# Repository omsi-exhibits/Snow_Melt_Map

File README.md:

# Snow Melt Map Notes
The electronics consist of a custom button controller pcb titled 8x_button_io_board that sends button press
commands to a octoWS2811 adapter with a teensy 4.0 socketed in it. The data sent over serial hand twisted
cable that is around 7 feet long. At a baud rate of 9600. 

addressable rgb led channels with a mcu to control the leds. The current mcu is Adafruit ItsyBitsy M0 express
with a plan to switch to a Teensy 4.0 if more pins or processing power is needed.

## Folder organization
- pcb :: contains eagle pcb files: 8x_button_io_board
- src :: main source code for the led controller 
- docs :: documentation, system diagram, map_led_hole numbering, river_segment_indexes, data sheets
- button_controller_arduino :: code for the button controller
- audio :: audio assets to be used with the wavTrigger board
- examples_tests :: quick tests used to guide prototype direction

## Led Lights
WS2813B  WS2812 code compatible. These leds have 2 data channels incase one led breaks the
backup data channel will be used. This allows the strip to skip a bad led and continue.

## Power Calculations
550 leds 48ma each LED when light at max. The led strings come in 50 led segments. We need power injection every 50 leds at least.
So that is 11 + 1 the end of the strip. 50 Leds at 48mA is 2.4A.

### Total Max Power usage
550 leds * 48mA = 26400mA, If all the leds are on at full brightness.
Power supply is a LRS-200-5 5v 200W output
(Wire Ampacity) [https://en.wikipedia.org/wiki/American_wire_gauge#Tables_of_AWG_wire_sizes]

### Fused Power distro board
(falcon f-8 power distro board) [https://www.pixelcontroller.com/store/accessories/46-f8-distro.html]
There are two power distribution boards with 8 5A fuse holders. The fuse holders take mini blade ATX fuses.

Useful fuse links
(all about fuses for led projects) [https://www.doityourselfchristmas.com/wiki/index.php?title=Power_Supplies#Using_Fuses_and_Fuseholders]
(assorted fuses) [https://www.amazon.com/Bussmann-NO-43-Blade-Tester-Puller/dp/B000DCN9BW]
(fuse holder board mount) [https://www.keyelco.com/product.cfm/Mini-Auto-Fuse-Holders/3544-2/product_id/1376]
(fuse holder mini ATM) [https://www.digikey.com/en/products/detail/keystone-electronics/3568/2137306]

# SNOW MELT MAP Button Target Areas
// Button 1 - Colorado R. & Tributaries
// --- R14 - R34
// Button 2 - Snow Monitoring Sites
// Button 3 - Dams (7)
// Button 4 - Los Vegas City, Dams, and river segments feeding Los Vegas. 
// --- R14 - R30 light up & 4 Dams (Lighting up Damns seems wrong, but maybe okay)
// Button 5 - Farms
// Button 6 - Grand Junction City, Dam, and rivers to the right of the city leading into it
// --- R21b (sub segment) (0-12leds) & R22, Dam
// Button 7 - Greater Los Angeles water supply
// --- Aqueducts too
// --- All river supply. exclude R34
// Button 8 -  (Long-distance water users) Outside Colorado r. Watershed
// --- All Water supply areas.

Once a button is pressed  - Only 1 button may be active at a time.
UI - dim all the currently lit segments and lights then activate what was pressed
Good opportunity for a fade in and fade out sound.

If the on button is pressed it turns the feature off.
If left on after a set time it can return to attractor mode. 

## Programing Notes
LedSegment defines a segment of leds, and their connection point to others.
LedRegion collects LedSegments and has state. The LedRegion can be interacted with.
- TurnedOn, TurnedOff, RiverOn, RiverOff.
- LedModule(Segment) that are for the Dams, etc. Should not store color data in their object.

## FastLED notes:
Colors are always dimmed down by a fraction. The dimming fraction is expressed in 256ths, so if you wanted to dim a color down by 25% of its current brightness, you first have to express that in 256ths. In this case, 25% = 64/256.
```cpp
  // Dim a color by 25% (64/256ths)
  // using "video" scaling, meaning: never fading to full black
  leds[i].fadeLightBy( 64 );
```
The library also provides a function that lets you 'clamp' each of the RGB channels to be within given minimums and maximums. 

Blending colors amountOfP2 is 0 - 255. 128 is 50% 255 is 100 color p2.
```cpp 
CRGB 	blend (const CRGB &p1, const CRGB &p2, fract8 amountOfP2)
```

## Hardware Purchased:
[WS2813 LEDs from raywu](https://www.aliexpress.com/item/32733155461.html)
[Aliexpress Neopixel store - Ray Wu](https://www.aliexpress.com/store/701799?spm=a2g0o.detail.1000002.2.75cff4f3j9F8uI)
LRS-200-5

## LED quality testing
I have determined that the last batch of hardware had some defects that likely were contributing to the intermittent problems
with leds flickering and possible temperature based issues.
We ordered more led strands to try to solve the issue. This time we got about 2x the leds we will need incase we run into the
same issues and need to pick the best leds from the pack.

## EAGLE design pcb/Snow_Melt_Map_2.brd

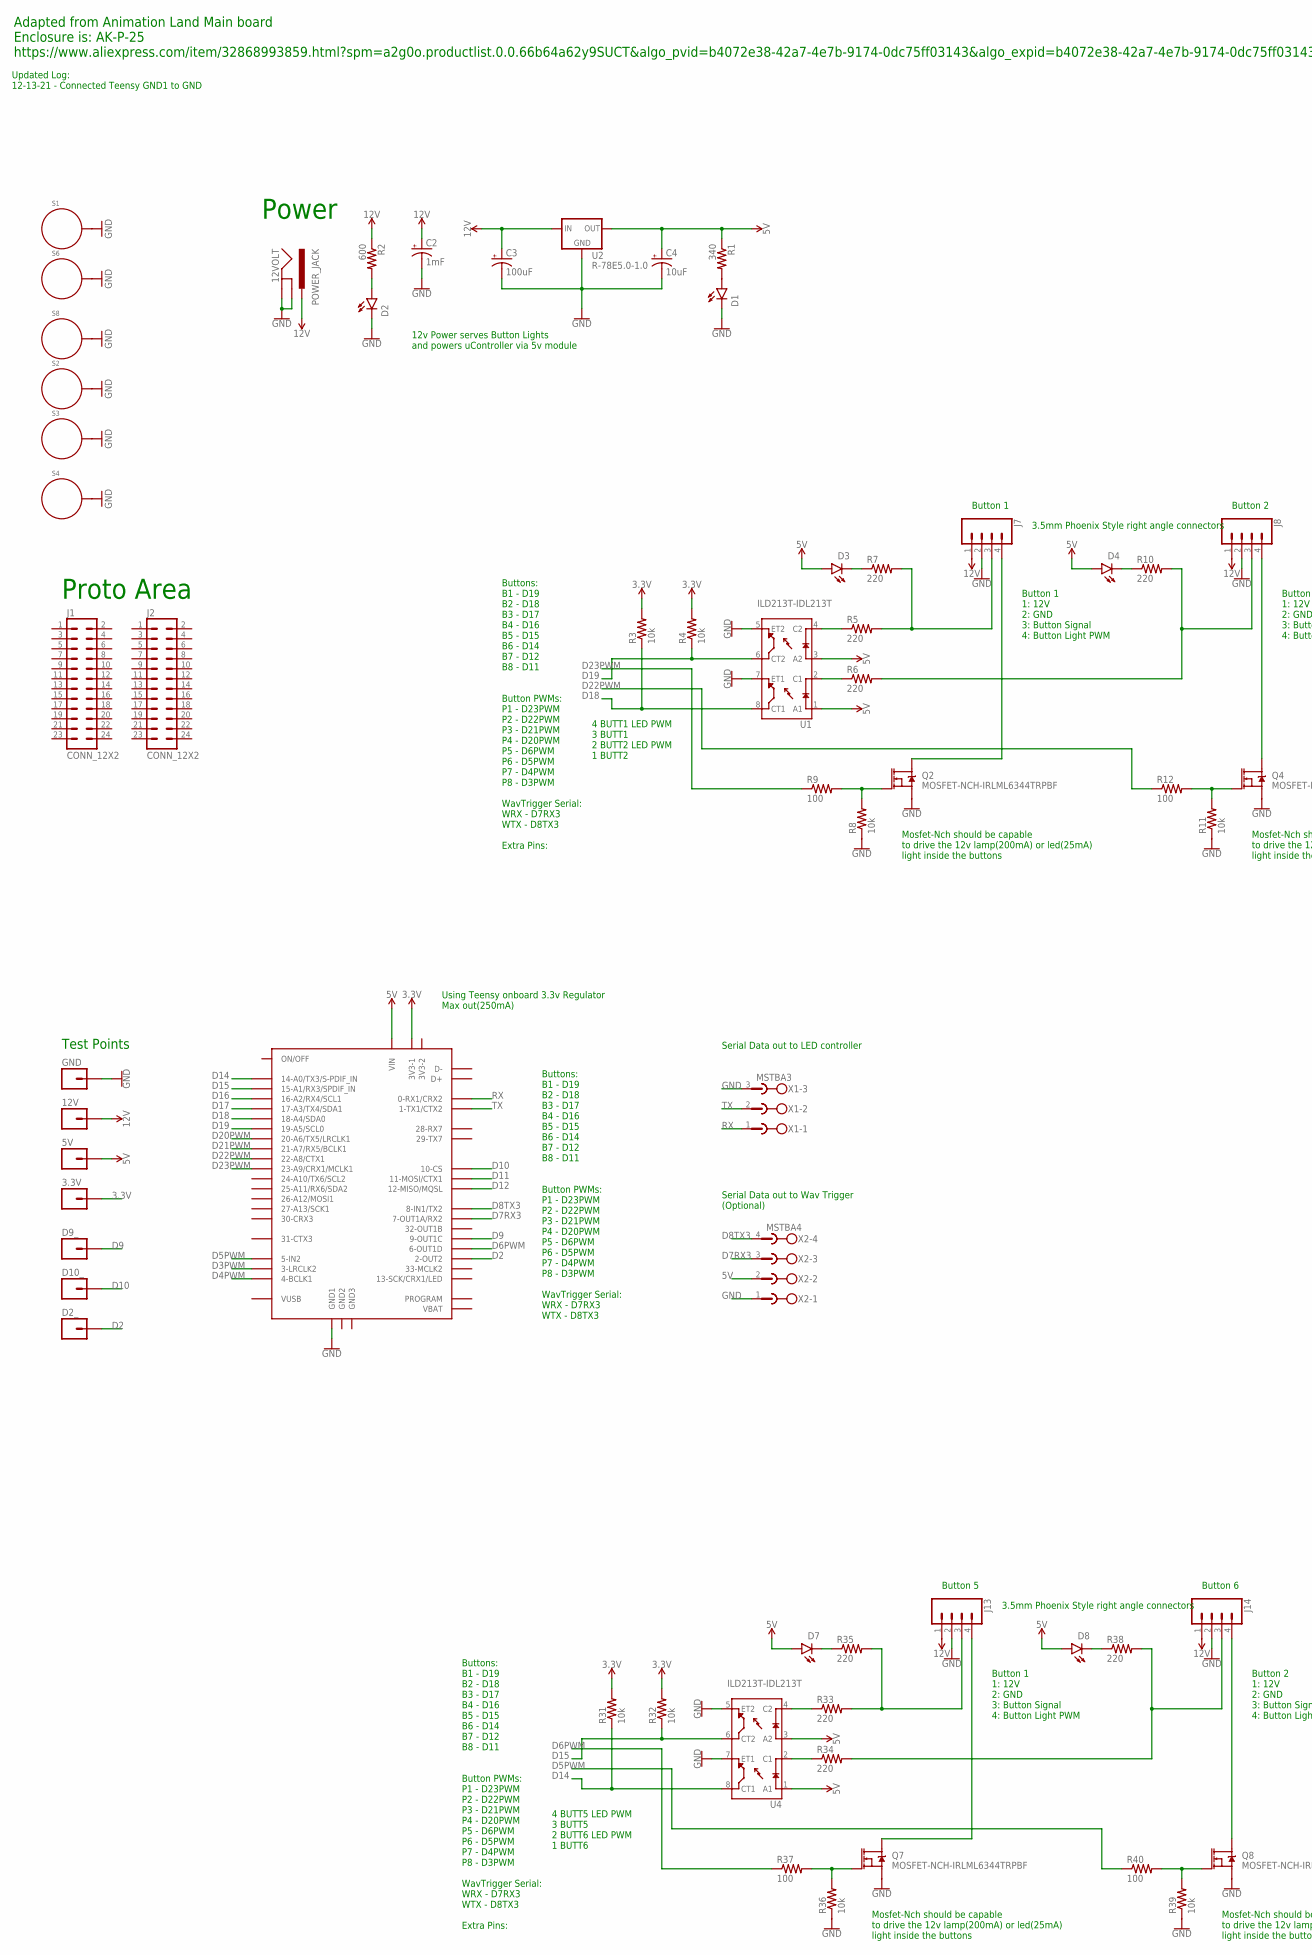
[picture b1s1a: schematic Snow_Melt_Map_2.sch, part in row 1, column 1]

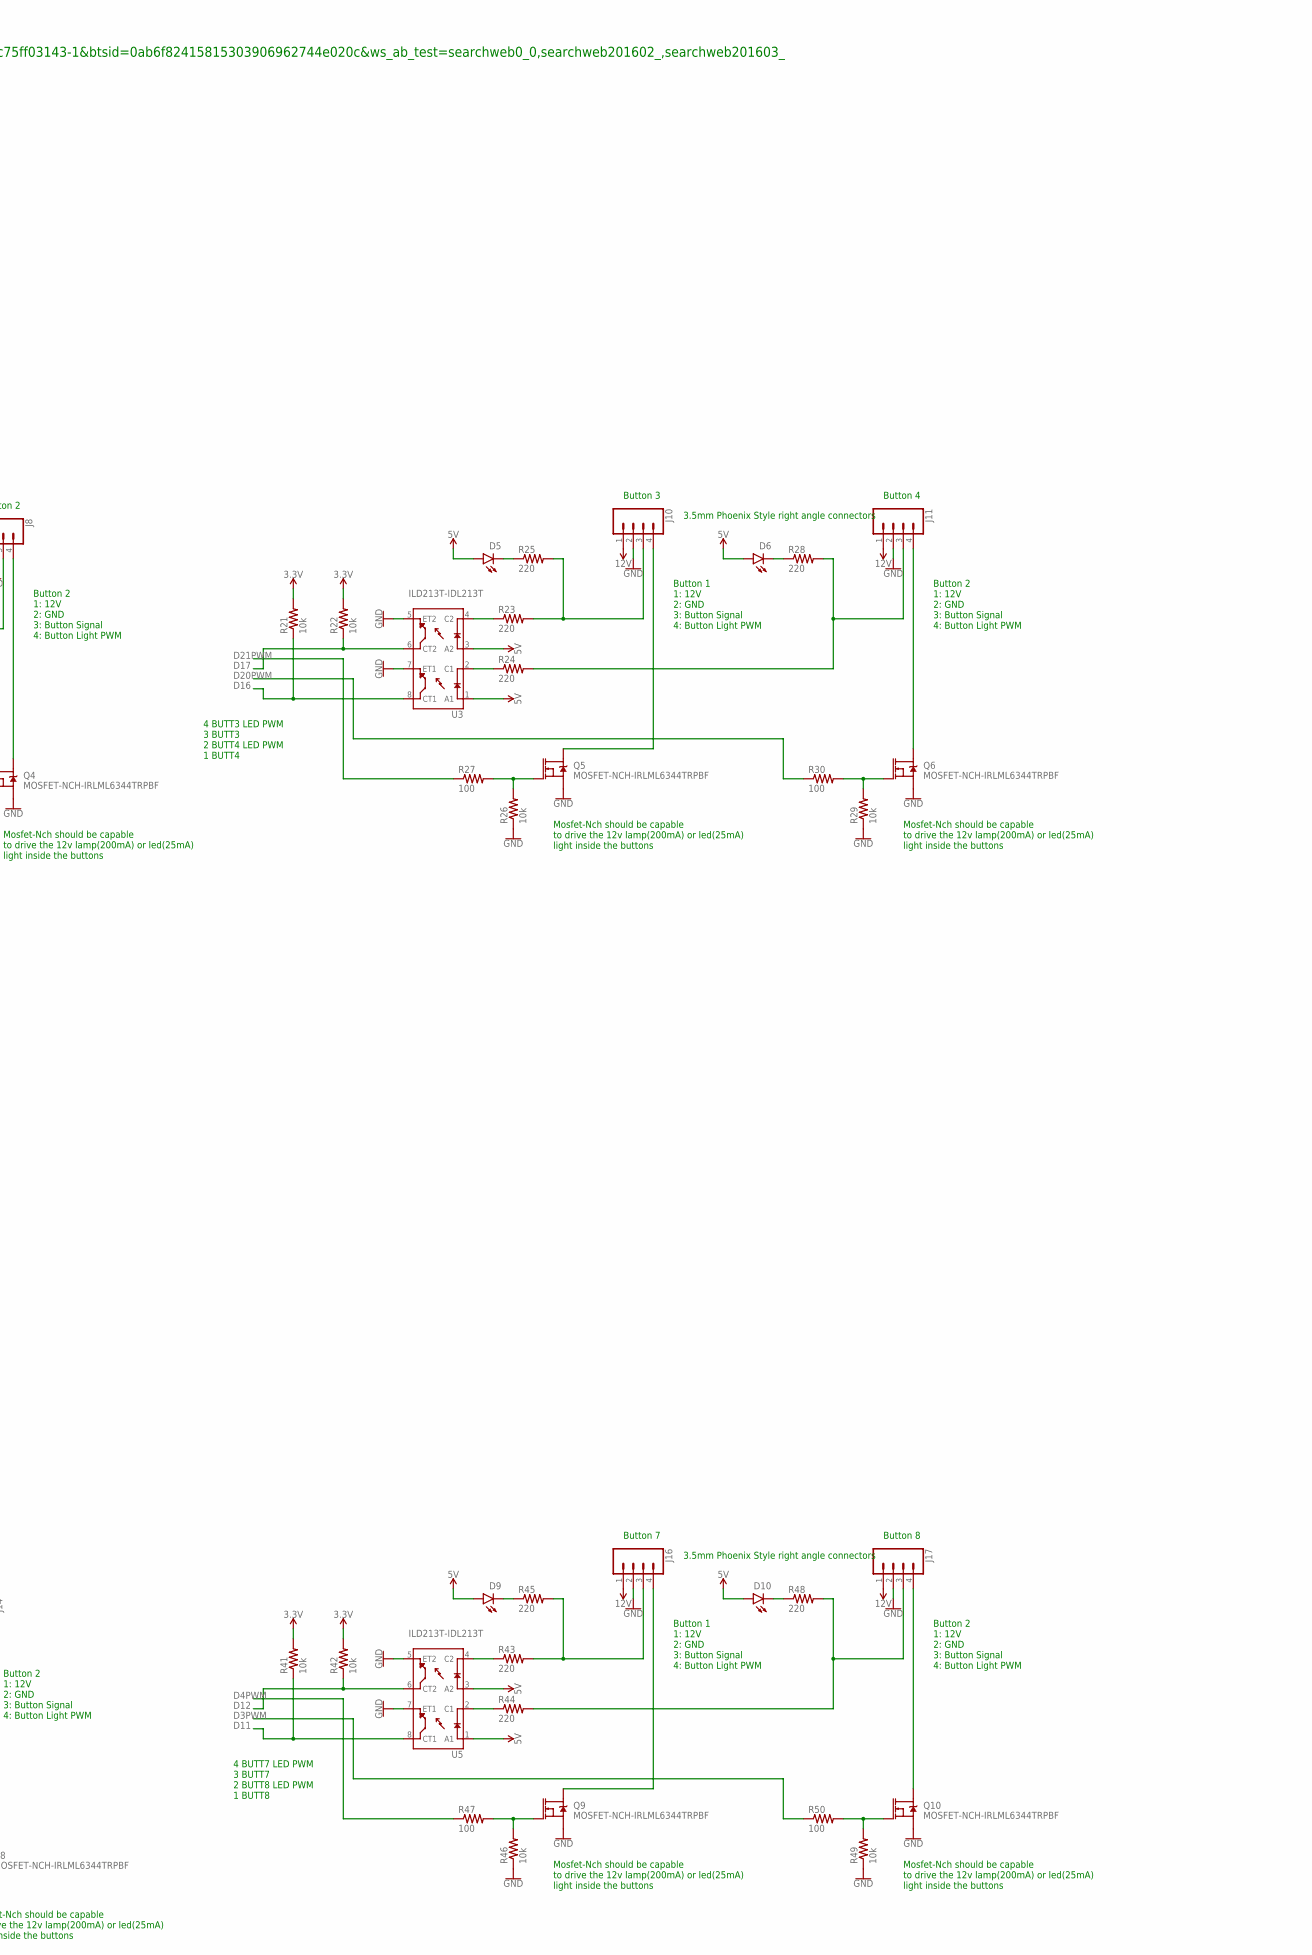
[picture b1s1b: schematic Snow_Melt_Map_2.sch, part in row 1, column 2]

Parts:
3.3V, 5V, 12V: M01PTH; 1X01
12VOLT: POWER_JACK; POWER_JACK_PTH
C2: 1mF; CPOL-RADIAL-5MM-10MM
C3: 100uF; CPOL-RADIAL-2.5MM-6.5MM
C4: 10uF; CPOL-RADIAL-2.5MM-5MM-KIT
D1, D2, D3, D4, D5, D6, D7, D8, D9, D10: RED; LED-1206
D2_, D9_, D10_: M01PTH; 1X01
GND: M01PTH; 1X01
J1, J2: CONN_12X2; 2X12
J7, J8, J10, J11, J13, J14, J16, J17: CONN_043.5MM_RA; 1X04_3.5MM_RA
Q2, Q4, Q5, Q6, Q7, Q8, Q9, Q10: MOSFET-NCH-IRLML6344TRPBF; SOT23-3
R1: 340; R0805
R2: 600; R0805
R3, R4, R8, R11, R21, R22, R26, R29, R31, R32, R36, R39, R41, R42, R46, R49: 10k; R0805
R5, R6, R7, R10, R23, R24, R25, R28, R33, R34, R35, R38, R43, R44, R45, R48: 220; R0805
R9, R12, R27, R30, R37, R40, R47, R50: 100; R0805
S1, S2, S3, S4, S6, S8: STANDOFF_ELECTRICAL5-32; STANDOFF_ELECTRICAL_5_32
U1, U3, U4, U5: ILD213T-IDL213T; SO08
U2: R-78E5.0-1.0; DC-DC_CONVERTER_78XX
U$1: TEENSY40
X1: MSTBA3
X2: MSTBA4

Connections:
3.3V: 3.3V.1, R3.2, R4.2, R21.2, R22.2, R31.2, R32.2, R41.2, R42.2, U$1.3V3-1
5V: 5V.1, C4.1 (+), D3.A, D4.A, D5.A, D6.A, D7.A, D8.A, D9.A, D10.A, R1.1, U1.1 (A1), U1.3 (A2), U2.VOUT (OUT), U3.1 (A1), U3.3 (A2), U4.1 (A1), U4.3 (A2), U5.1 (A1), U5.3 (A2), U$1.VIN, X2.2
12V: 12V.1, 12VOLT.PWR, C2.+, C3.1 (+), J7.1, J8.1, J10.1, J11.1, J13.1, J14.1, J16.1, J17.1, R2.1, U2.VIN (IN)
D2: D2_.1, U$1.2-OUT2
D3PWM: R50.1, U$1.3-LRCLK2
D4PWM: R47.1, U$1.4-BCLK2 (4-BCLK1)
D5PWM: R40.1, U$1.5-IN2
D6PWM: R37.1, U$1.6-OUT1D
D7RX3: U$1.7-RX2/OUT1A (7-OUT1A/RX2), X2.3
D8TX3: U$1.8-TX2/IN1 (8-IN1/TX2), X2.4
D9: D9_.1, U$1.9-OUT1C
D10: D10_.1, U$1.10-CS/MQSR (10-CS)
D11: R41.1, U5.8 (CT1), U$1.11-MOSI/CTX1
D12: R42.1, U5.6 (CT2), U$1.12-MIO/MQSL (12-MISO/MQSL)
D14: R31.1, U4.8 (CT1), U$1.14-A0/TX3/S-PFI_OUT (14-A0/TX3/S-PDIF_IN)
D15: R32.1, U4.6 (CT2), U$1.15-A1/RX3/S-PDIF_IN (15-A1/RX3/SPDIF_IN)
D16: R21.1, U3.8 (CT1), U$1.16-A2/RX4/SCL1
D17: R22.1, U3.6 (CT2), U$1.17-A3/TX4/SDA1
D18: R3.1, U1.8 (CT1), U$1.18-A4/SDA0
D19: R4.1, U1.6 (CT2), U$1.19-A5/SCL0
D20PWM: R30.1, U$1.20-A6/TX5/LRCLK1
D21PWM: R27.1, U$1.21-A7/RX5/BCLK1
D22PWM: R12.1, U$1.22-A8/CTX1
D23PWM: R9.1, U$1.23-A9/CRX1/CCLK1 (23-A9/CRX1/MCLK1)
GND: 12VOLT.GND, 12VOLT.GNDBREAK, C2.-, C3.2 (-), C4.2 (-), D1.C, D2.C, GND.1, J7.2, J8.2, J10.2, J11.2, J13.2, J14.2, J16.2, J17.2, Q2.2 (S), Q4.2 (S), Q5.2 (S), Q6.2 (S), Q7.2 (S), Q8.2 (S), Q9.2 (S), Q10.2 (S), R8.1, R11.1, R26.1, R29.1, R36.1, R39.1, R46.1, R49.1, S1.P1, S2.P1, S3.P1, S4.P1, S6.P1, S8.P1, U1.5 (ET2), U1.7 (ET1), U2.GND, U3.5 (ET2), U3.7 (ET1), U4.5 (ET2), U4.7 (ET1), U5.5 (ET2), U5.7 (ET1), U$1.GND1, X1.3, X2.1
unnamed: D1.A, R1.2
unnamed: D2.A, R2.2
unnamed: J7.3, R5.2, R7.2
unnamed: D3.C, R7.1
unnamed: R5.1, U1.4 (C2)
unnamed: R6.1, U1.2 (C1)
unnamed: Q2.1 (G), R8.2, R9.2
unnamed: J7.4, Q2.3 (D)
unnamed: J8.3, R6.2, R10.2
unnamed: D4.C, R10.1
unnamed: Q4.1 (G), R11.2, R12.2
unnamed: J8.4, Q4.3 (D)
unnamed: J10.3, R23.2, R25.2
unnamed: D5.C, R25.1
unnamed: R23.1, U3.4 (C2)
unnamed: R24.1, U3.2 (C1)
unnamed: Q5.1 (G), R26.2, R27.2
unnamed: J10.4, Q5.3 (D)
unnamed: J11.3, R24.2, R28.2
unnamed: D6.C, R28.1
unnamed: Q6.1 (G), R29.2, R30.2
unnamed: J11.4, Q6.3 (D)
unnamed: J13.3, R33.2, R35.2
unnamed: D7.C, R35.1
unnamed: R33.1, U4.4 (C2)
unnamed: R34.1, U4.2 (C1)
unnamed: Q7.1 (G), R36.2, R37.2
unnamed: J13.4, Q7.3 (D)
unnamed: J14.3, R34.2, R38.2
unnamed: D8.C, R38.1
unnamed: Q8.1 (G), R39.2, R40.2
unnamed: J14.4, Q8.3 (D)
unnamed: J16.3, R43.2, R45.2
unnamed: D9.C, R45.1
unnamed: R43.1, U5.4 (C2)
unnamed: R44.1, U5.2 (C1)
unnamed: Q9.1 (G), R46.2, R47.2
unnamed: J16.4, Q9.3 (D)
unnamed: J17.3, R44.2, R48.2
unnamed: D10.C, R48.1
unnamed: Q10.1 (G), R49.2, R50.2
unnamed: J17.4, Q10.3 (D)
RX: U$1.0-RX1 (0-RX1/CRX2), X1.1
TX: U$1.1-TX1 (1-TX1/CTX2), X1.2

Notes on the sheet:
Adapted from Animation Land Main board Enclosure is: AK-P-25 https://www.aliexpress.com/item/32868993859.html?spm=a2g0o.productlist.0.0.66b64a62y9SUCT&algo_pvid=b4072e38-42a7-4e7b-9174-0dc75ff03143&algo_expid=b4072e38-42a7-4e7b-9174-0dc75ff03143-1&btsid=0ab6f82415815303906962744e020c&ws_ab_test=sea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
Proto Area
Mosfet-Nch should be capable to drive the 12v lamp(200mA) or led(25mA) light inside the buttons
4 BUTT1 LED PWM 3 BUTT1 2 BUTT2 LED PWM 1 BUTT2
Button 1 1: 12V 2: GND 3: Button Signal 4: Button Light PWM
Button 2 1: 12V 2: GND 3: Button Signal 4: Button Light PWM
3.5mm Phoenix Style right angle connectors
Button 1
Button 2
4 BUTT3 LED PWM 3 BUTT3 2 BUTT4 LED PWM 1 BUTT4
Button 3
Button 4
4 BUTT5 LED PWM 3 BUTT5 2 BUTT6 LED PWM 1 BUTT6
Button 5
Button 6
4 BUTT7 LED PWM 3 BUTT7 2 BUTT8 LED PWM 1 BUTT8
Button 7
Button 8
12v Power serves Button Lights and powers uController via 5v module
Power
Buttons: B1 - D19 B2 - D18 B3 - D17 B4 - D16 B5 - D15 B6 - D14 B7 - D12 B8 - D11 Button PWMs: P1 - D23PWM P2 - D22PWM P3 - D21PWM P4 - D20PWM P5 - D6PWM P6 - D5PWM P7 - D4PWM P8 - D3PWM WavTrigger Serial: WRX - D7RX3 WTX - D8TX3
Using Teensy onboard 3.3v Regulator Max out(250mA)
Buttons: B1 - D19 B2 - D18 B3 - D17 B4 - D16 B5 - D15 B6 - D14 B7 - D12 B8 - D11 Button PWMs: P1 - D23PWM P2 - D22PWM P3 - D21PWM P4 - D20PWM P5 - D6PWM P6 - D5PWM P7 - D4PWM P8 - D3PWM WavTrigger Serial: WRX - D7RX3 WTX - D8TX3 Extra Pins:
Serial Data out to LED controller
Test Points
Serial Data out to Wav Trigger (Optional)
Updated Log: 12-13-21 - Connected Teensy GND1 to GND

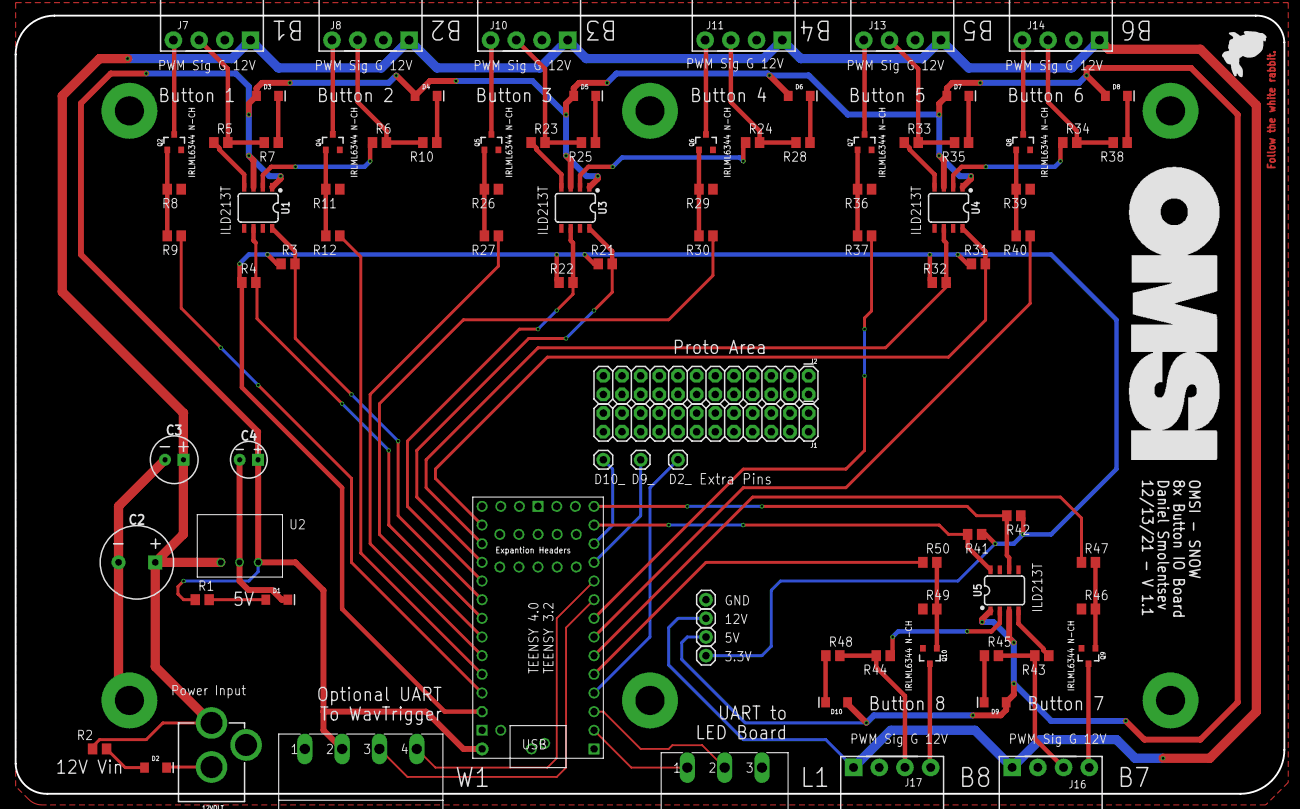
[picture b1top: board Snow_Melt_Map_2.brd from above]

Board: 2 copper layers, 172.7 x 105.9 mm, 95 parts (0 on the bottom side), 69 nets.

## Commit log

2021-06-03 Initial commit. Proof of concept. Basic DMA Neopixel on pin 12
2021-06-03 Updated README info
2021-06-03 Added a basic Input system
2021-06-08 Added Holes Map documentation and Segments Indexes spread sheet
2021-06-09 Led Segments implemented. Led River Marque animation.
2021-06-10 Multi LedSegment LedModule almost works
2021-06-10 Multi Segment LedModule is working.
2021-06-14 added more leds to the output to troubleshoot
2021-06-14 Seems to work without flickering! Had to add capacitors at power splice points.
2021-06-21 continued power issues, investigation.
2021-06-24 Sanity. Its working on Teensy 4.0 Octows2811-Top Jack LEDStrip#2
2021-07-07 minor edits
2021-07-07 fixed links in readme
2021-08-05 updated readme with LED quality inspection info
2021-09-02 Trying to get 2 led strings to work at once. only one works
2021-09-07 2 channels are working. Tweeked speeds and Notes
2021-10-20 starting to cleanup
2021-10-20 Removed ItsyBitsy env from platformio
2021-10-20 added non-river ledSegments. Changed city color to orange
2021-10-21 all segments working, river is flowing with basic animations
2021-11-11 LedMap class added .. partially working
2021-11-23 Interactivity is in. Basic Button input. Updated docs. Still a few bugs
2021-11-24 FadeInWait setup, Attractor updated. MVP
2021-12-08 changed attractor to light up all 3 cities
2021-12-08 added all the outside docs and audio and teensy led tests
2021-12-22 fixed snowsite O16 and O15 (dam) switched.
2022-03-08 fixed map key not having correct color for snowsites and dams

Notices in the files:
parts and their libraries:
SparkFun-Connectors: Licensing: Creative Commons ShareAlike 4.0 International - https://creativecommons.org/licenses/by-sa/4.0
SparkFun-Connectors: Licensing: CC v3.0 Share-Alike You are welcome to use this library for commercial purposes.
